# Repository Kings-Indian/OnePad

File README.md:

# OnePad

**OnePad** is a custom macropad inspired by *One Piece*!

## Features

- 8 programmable keys  
- 1 rotary encoder  
- 1 OLED display  

## Gallery

## PCB

## Bill of Materials (BOM)

> For exact details, refer to `bom.csv`.

- 1× OLED display  
- 8× Keycaps  
- 8× Cherry MX switches  
- 8× SK6812 MINI-E LEDs  
- 9× Diodes  
- 1× Seeed Studio XIAO RP2040  
- 4× M3 5mm screws  
- 4× M3 8mm screws

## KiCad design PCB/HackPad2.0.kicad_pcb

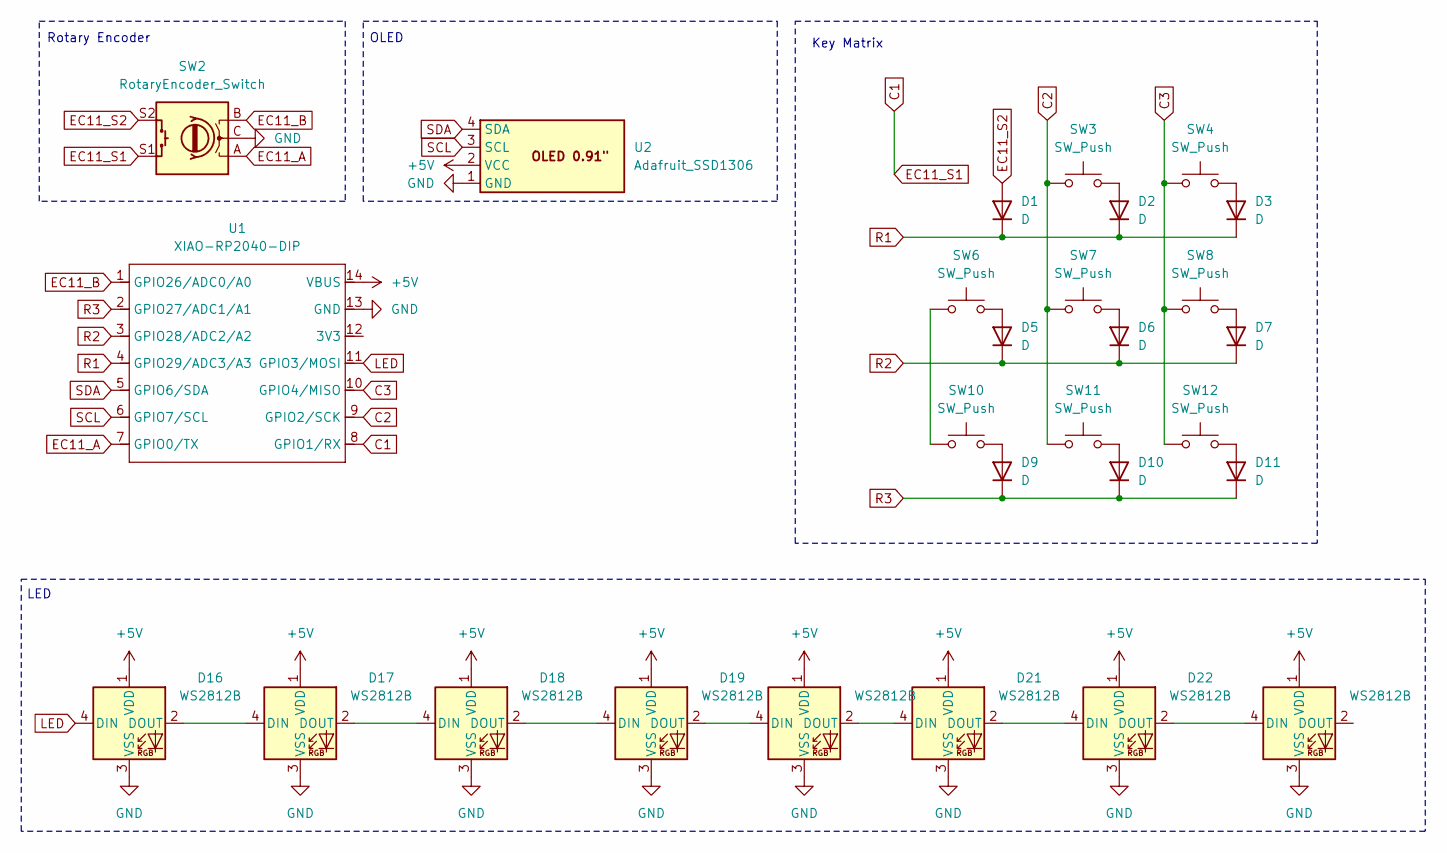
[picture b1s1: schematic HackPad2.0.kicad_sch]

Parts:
D1, D2, D3, D5, D6, D7, D9, D10, D11: D; D_DO-35_SOD27_P7.62mm_Horizontal
D16, D17, D18, D19, D20, D21, D22, D23: WS2812B; MX_SK6812MINI-E_REV
SW2: RotaryEncoder_Switch; RotaryEncoder_Alps_EC11E-Switch_Vertical_H20mm
SW3, SW4, SW6, SW7, SW8, SW10, SW11, SW12: SW_Push; SW_Cherry_MX_1.00u_PCB
U1: XIAO-RP2040-DIP; Seeed_XIAO_RP2040
U2: Adafruit_SSD1306; Module_OLED_091

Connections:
+5V: D16.1 (VDD), D17.1 (VDD), D18.1 (VDD), D19.1 (VDD), D20.1 (VDD), D21.1 (VDD), D22.1 (VDD), D23.1 (VDD), U1.14 (VBUS), U2.2 (VCC)
C1: SW2.S1, U1.8 (GPIO1/RX)
C2: SW3.1, SW7.1, SW11.1, U1.9 (GPIO2/SCK)
C3: SW4.1, SW8.1, SW12.1, U1.10 (GPIO4/MISO)
EC11_A: SW2.A, U1.7 (GPIO0/TX)
EC11_B: SW2.B, U1.1 (GPIO26/ADC0/A0)
EC11_S2: D1.2 (A), SW2.S2
GND: D16.3 (VSS), D17.3 (VSS), D18.3 (VSS), D19.3 (VSS), D20.3 (VSS), D21.3 (VSS), D22.3 (VSS), D23.3 (VSS), SW2.C, U1.13 (GND), U2.1 (GND)
LED: D16.4 (DIN), U1.11 (GPIO3/MOSI)
unnamed: D2.2 (A), SW3.2
unnamed: D3.2 (A), SW4.2
unnamed: D5.2 (A), SW6.2
unnamed: D6.2 (A), SW7.2
unnamed: D7.2 (A), SW8.2
unnamed: D9.2 (A), SW10.2
unnamed: D10.2 (A), SW11.2
unnamed: D11.2 (A), SW12.2
unnamed: D16.2 (DOUT), D17.4 (DIN)
unnamed: D17.2 (DOUT), D18.4 (DIN)
unnamed: D18.2 (DOUT), D19.4 (DIN)
unnamed: D19.2 (DOUT), D20.4 (DIN)
unnamed: D20.2 (DOUT), D21.4 (DIN)
unnamed: D21.2 (DOUT), D22.4 (DIN)
unnamed: D22.2 (DOUT), D23.4 (DIN)
unnamed: SW6.1, SW10.1
R1: D1.1 (K), D2.1 (K), D3.1 (K), U1.4 (GPIO29/ADC3/A3)
R2: D5.1 (K), D6.1 (K), D7.1 (K), U1.3 (GPIO28/ADC2/A2)
R3: D9.1 (K), D10.1 (K), D11.1 (K), U1.2 (GPIO27/ADC1/A1)
SCL: U1.6 (GPIO7/SCL), U2.3 (SCL)
SDA: U1.5 (GPIO6/SDA), U2.4 (SDA)

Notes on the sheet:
LED
Rotary Encoder
OLED
Key Matrix

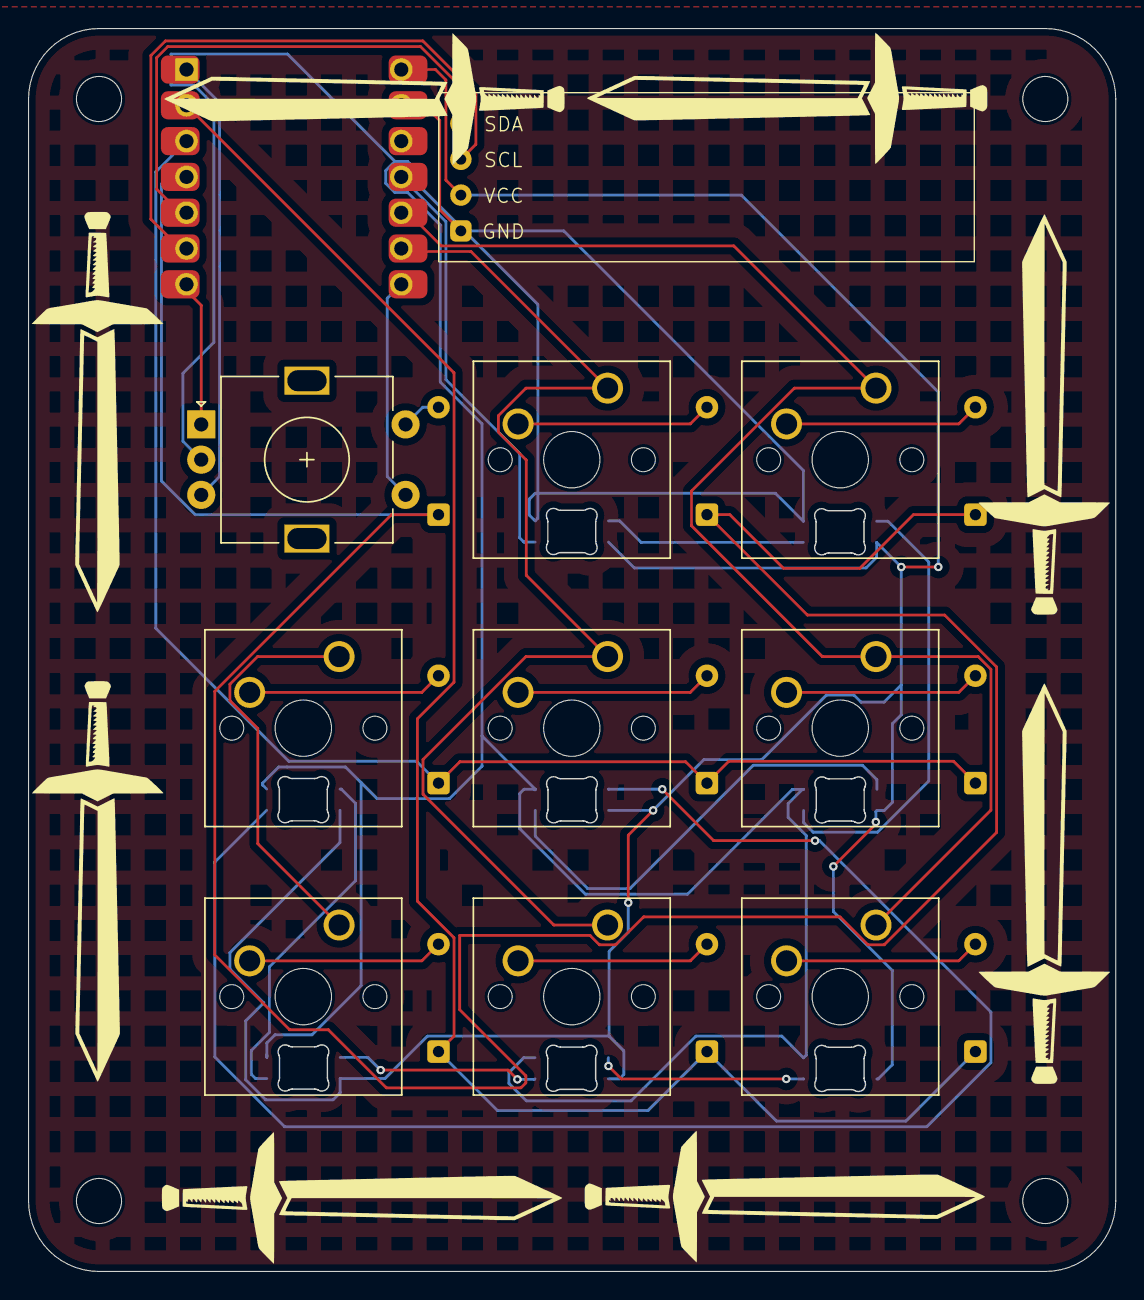
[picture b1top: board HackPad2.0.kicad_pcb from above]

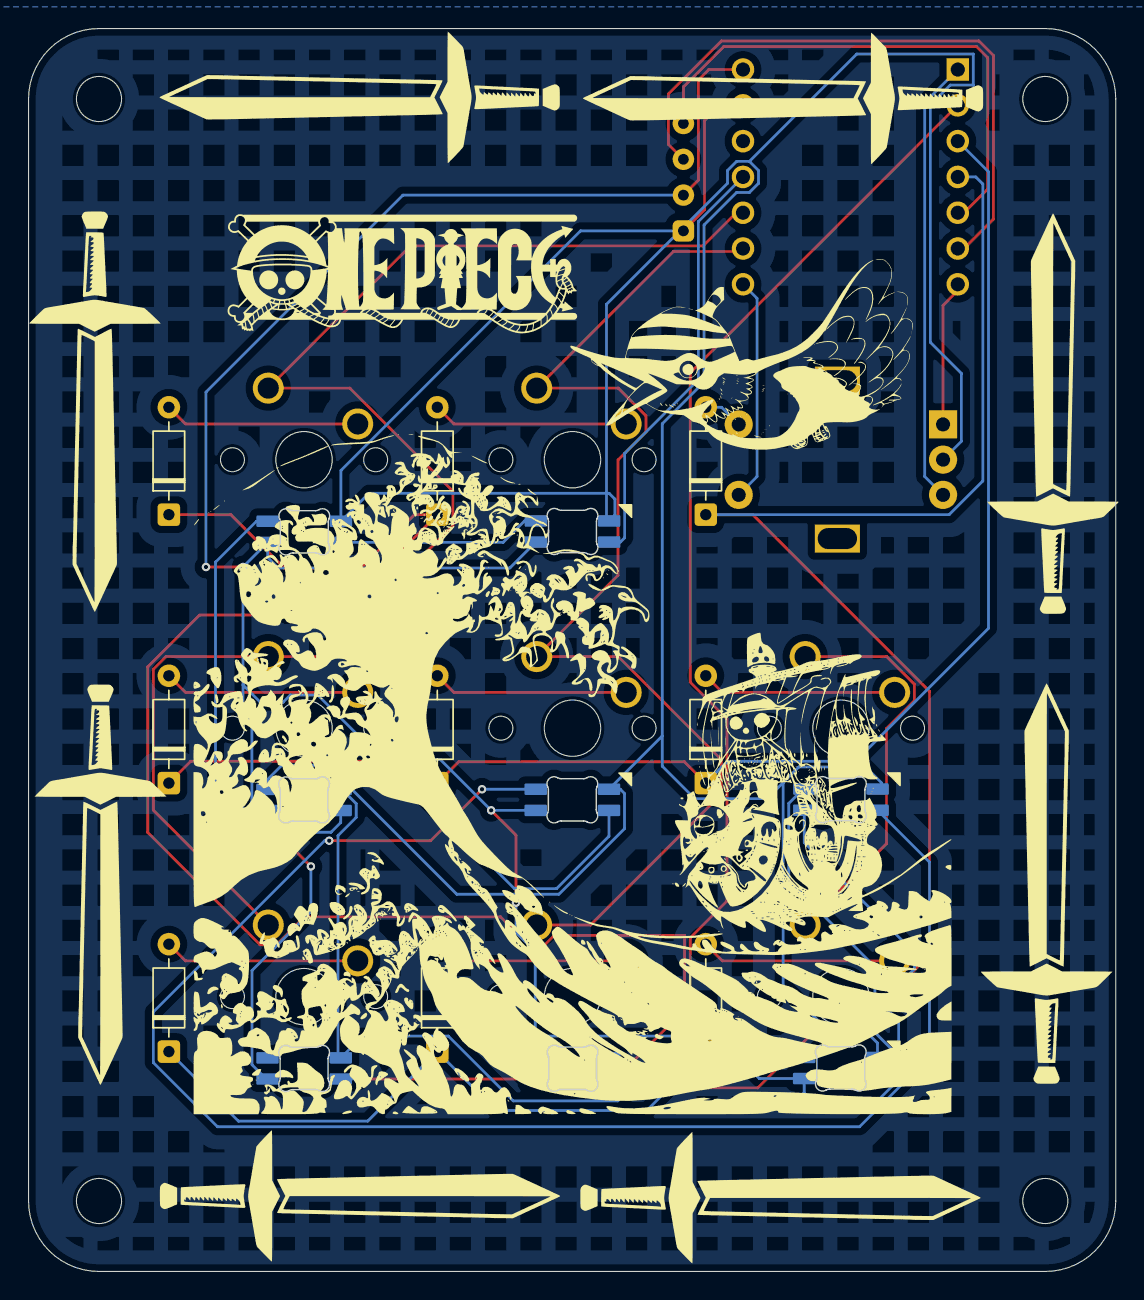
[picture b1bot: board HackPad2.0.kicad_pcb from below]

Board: 2 copper layers, 77.1 x 88.2 mm, 28 parts (9 on the bottom side), 30 nets.

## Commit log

2025-12-04 me make readme
    me make readme
2025-12-04 added files, nexrt me make BOM
2025-12-05 Add BOM entries with item details and pricing
